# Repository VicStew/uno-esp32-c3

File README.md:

# ESP32-C6 Dev Board
Personal project involving the creation of an ESP32-C6 Dev Board. 

The ESP32-C6 module comes equipped with:
* A 32-bit processor with a clock speed of upto 160 MHz. 
* Supports Wi-Fi 6 and bluetooth 5 (LE) with onboard antenna and thread, zigbee protocols.
* Comes with built in 320KB ROM, 512KB of HP SRAM, 16KB LP SRAM and 4MB Flash memory.
* Adapts multiple IO interfaces and integrates a full-speed USB PHY interface.

The Dev Board includes support for DC input power.

## Getting Started

## Development Environment Setup (Ubuntu)

This project supports firmware development for the **ESP32-C6** using both:

* **C/C++ with ESP-IDF** (official Espressif framework)
* **Rust with esp-rs** (modern, type-safe embedded development)

You can use either workflow independently.

---

## Option A: C/C++ Development (ESP-IDF)

ESP-IDF is Espressif’s official SDK and provides full, first-class support for the ESP32-C6.

### 1. Install System Dependencies

Update your system and install required packages:

```bash
sudo apt update
sudo apt install -y \
  git \
  python3 \
  python3-pip \
  python3-venv \
  cmake \
  ninja-build \
  libusb-1.0-0
```

Verify Python:

```bash
python3 --version
```

---

### 2. Install ESP-IDF

Clone ESP-IDF (recommended stable version):

```bash
git clone -b v5.2 --recursive https://github.com/espressif/esp-idf.git
```

Run the installer:

```bash
cd esp-idf
./install.sh esp32c6
```

Activate the ESP-IDF environment:

```bash
source export.sh
```

To make this persistent, you may add the above line to your `~/.bashrc` or `~/.zshrc`.

Verify installation:

```bash
idf.py --version
```

---

### 3. First Hello World (C/C++)

Create a new project:

```bash
idf.py create-project hello_world
cd hello_world
```

Set the target to ESP32-C6:

```bash
idf.py set-target esp32c6
```

(Optional) Configure the project:

```bash
idf.py menuconfig
```

Important settings:

* Serial port selection
* Flash size (if your PCB differs from defaults)

Build, flash, and monitor:

```bash
idf.py build
idf.py flash monitor
```

Expected serial output:

```
Hello world!
```

Your toolchain is alive and talking.

---

## Option B: Rust Development (esp-rs)

Rust development uses the esp-hal ecosystem and the RISC-V toolchain for ESP32-C6.

---

### 1. Install Rust

Install Rust using `rustup`:

```bash
curl --proto '=https' --tlsv1.2 -sSf https://sh.rustup.rs | sh
```

Reload your shell:

```bash
source ~/.cargo/env
```

Install required components:

```bash
rustup component add rust-src
```

---

### 2. Install ESP Rust Toolchain

Install the ESP toolchain manager:

```bash
cargo install espup
```

Install ESP targets and tools:

```bash
espup install
```

Activate the environment:

```bash
source ~/export-esp.sh
```

Add the ESP32-C6 target:

```bash
rustup target add riscv32imac-unknown-none-elf
```

---

### 3. First Hello World (Rust)

Install the project generator:

```bash
cargo install esp-generate
```

Create a new project:

```bash
cargo generate esp-rs/esp-template
```

During setup:

* Select **esp32c6**
* Choose **no_std**
* Enable **UART logging**

Navigate into the project:

```bash
cd your_project_name
```

Build and flash:

```bash
cargo run
```

Expected output over serial:

```
Hello world from Rust!
```

Rust is officially on the board 🦀.

---

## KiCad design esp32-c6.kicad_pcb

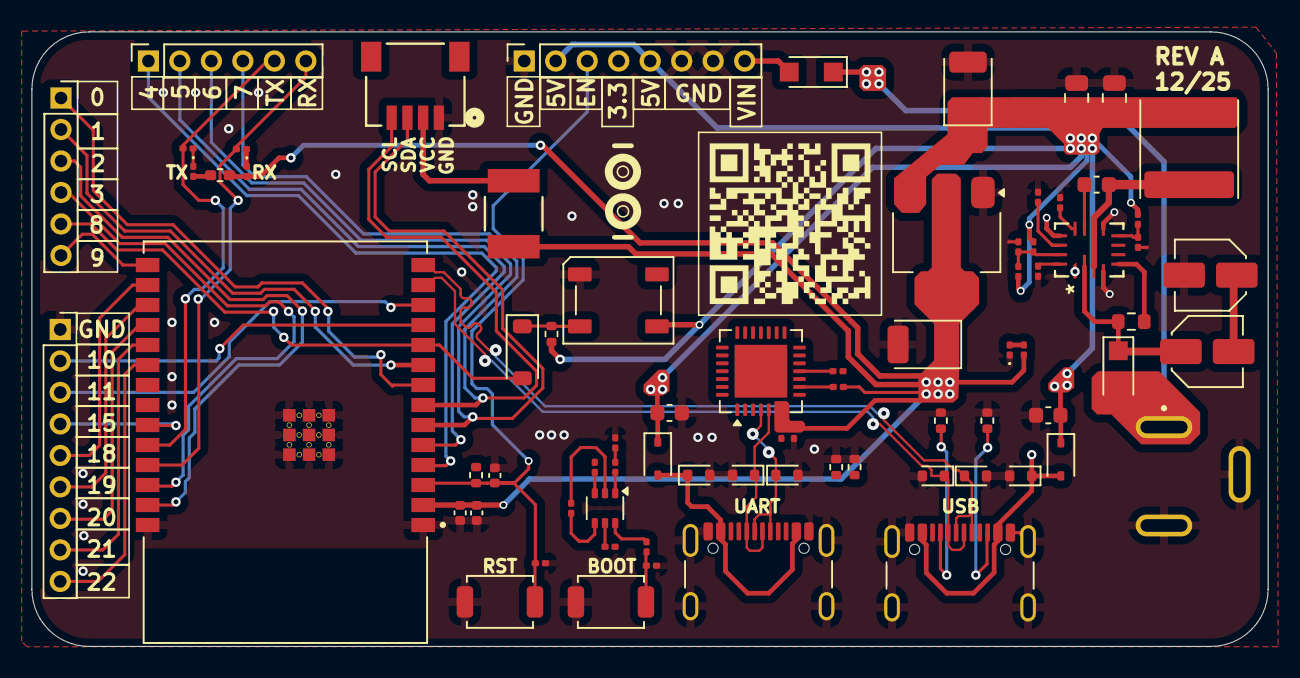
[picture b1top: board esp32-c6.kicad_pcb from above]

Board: 2 copper layers, 78.5 x 39.0 mm, 75 parts (0 on the bottom side), 60 nets.

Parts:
C1, C2: 10u/25V; C_0603_1608Metric
C3: 4.7u; C_0201_0603Metric
C4, C5, C6: 0.1u; C_0201_0603Metric
C7: 1u; C_0402_1005Metric
C8: 0.1u; C_0603_1608Metric
C9, C10: 22u, 25V; C_Elec_4x5.4
C11: 10p; C_0201_0603Metric
C12, C13: 22u; C_0805_2012Metric
C14, C17: 1u; C_0201_0603Metric
C15: 4.7n; C_0201_0603Metric
C16, C18: 10u; CP_EIA-3528-12_Kemet-T
C19: 0.1u; C_0402_1005Metric
C20: 10u; C_0402_1005Metric
D1, D2, D3, D4, D5, D13: ESD5Zxx; D_SOD-523
D6, D14: 1N5819WS; D_SOD-323
D7: 1N4148W; D_SOD-123
D8: WS2812B; LED_WS2812B_PLCC4_5.0x5.0mm_P3.2mm
D9, D10: PMEG6020AELR; Nexperia_CFP3_SOD-123W
D11, D12, D15: LED; LED_0201_0603Metric
F1: Polyfuse; FUSE_F050-2
J1, J2: USB_C_Receptacle_USB2.0_14P; USB_C_Receptacle_GCT_USB4105-xx-A_16P_TopMnt_Horizontal
J3: 54-00166; TENSILITY_54-00166
J4: Conn_01x08_Socket; PinSocket_1x08_P2.00mm_Vertical
J5, J8: Conn_01x06_Socket; PinSocket_1x06_P2.00mm_Vertical
J6: Conn_01x04; CONN_SM04B-SRSS-TB_JST
J9: Conn_01x09_Socket; PinSocket_1x09_P2.00mm_Vertical
L1: 10u; L_Changjiang_FNR6045S
Q1: BC847BDW1; SOT-363_SC-70-6
R1, R2, R3, R4: 5.1k; R_0402_1005Metric
R5, R15: 10k; R_0402_1005Metric
R6: 0; R_0402_1005Metric_Pad0.72x0.64mm_HandSolder
R7: 1k; R_0201_0603Metric
R8, R12, R13: 0; R_0201_0603Metric
R9, R10, R11, R14: 10k; R_0201_0603Metric
R16: 68.1k; R_0201_0603Metric
R17: 13k; R_0201_0603Metric
R18: 100k; R_0603_1608Metric
R19: 169k; R_0201_0603Metric
R20: 10; R_0201_0603Metric
R21, R22: 330; R_0201_0603Metric
R23: 5.1k; R_0201_0603Metric
SW1, SW2: SW_Push; SW_SPST_TS-1088-xR020
U1: CP2102N-Axx-xQFN28; QFN-28-1EP_5x5mm_P0.5mm_EP3.35x3.35mm
U2: MPQ9841GLE-5-AEC1-Z; QFN-16_MPQ9841
U3: NCP1117-3.3_SOT223; SOT-223-3_TabPin2
U4: ESP32-C6-WROOM-1-N8; XCVR_ESP32-C6-WROOM-1-N8

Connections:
+3.3V: C3.1, C4.1, C18.1, C19.1, C20.1, D11.2 (A), D12.2 (A), F1.2, J4.4, R6.1, R6.2, R7.1, R15.1, R23.1, U1.6 (VDD), U1.7 (VREGIN), U3.2 (VO), U4.2 (3V3)
+5V: C1.1, C2.1, C11.1, C12.1, C13.1, C16.1, D6.1 (K), D8.1 (VDD), D14.1 (K), J4.2, J4.5, L1.2, R5.1, R16.1, R20.1, U3.3 (VI)
/Barrel Jack/<NO NET>: C8.2, L1.1, U2.3 (SW), U2.10 (SW)
/Barrel Jack/BIAS: C17.1, R20.2, U2.8 (BIAS)
/Barrel Jack/BST: C8.1, U2.11 (BST)
/Barrel Jack/EN: R18.2, U2.5 (EN)
/Barrel Jack/FREQ: R19.1, U2.16 (FREQ)
/Barrel Jack/VOUT: C11.2, R16.2, R17.1, U2.15 (VOUT)
/DA_N: D5.1 (K), J1.A7 (D-), J1.B7 (D-), U1.5 (D-)
/DA_P: D3.1 (K), J1.A6 (D+), J1.B6 (D+), U1.4 (D+)
/DTR: R9.2, R11.2, U1.28 (~DTR)
/GPIO9: C5.2, R8.1, SW1.2
/RTS: Q1.4 (E2), R10.1, U1.24 (~RTS)
/esp32-c6 Pinout/IO0: J5.1, U4.8 (IO0)
/esp32-c6 Pinout/IO1: J5.2, U4.9 (IO1)
/esp32-c6 Pinout/IO2: J5.3, U4.27 (IO2)
/esp32-c6 Pinout/IO3: J5.4, U4.26 (IO3)
/esp32-c6 Pinout/IO4_TMS: J8.1, U4.4 (IO4)
/esp32-c6 Pinout/IO5_TDI: J8.2, U4.5 (IO5)
/esp32-c6 Pinout/IO6_SDA: J6.3, J8.3, U4.6 (IO6)
/esp32-c6 Pinout/IO7_SCL: J6.4, J8.4, U4.7 (IO7)
/esp32-c6 Pinout/IO9_BOOT: J5.6, U4.15 (IO9)
/esp32-c6 Pinout/IO10: J9.2, U4.11 (IO10)
/esp32-c6 Pinout/IO11: J9.3, U4.12 (IO11)
/esp32-c6 Pinout/IO15: J9.4, U4.23 (IO15)
/esp32-c6 Pinout/IO18: J9.5, U4.16 (IO18)
/esp32-c6 Pinout/IO19: J9.6, U4.17 (IO19)
/esp32-c6 Pinout/IO20: J9.7, U4.18 (IO20)
/esp32-c6 Pinout/IO21: J9.8, U4.19 (IO21)
/esp32-c6 Pinout/IO22: J9.9, U4.20 (IO22)
/esp32-c6 Pinout/UART_RX: J8.6, R22.2, U4.25 (TXD0/GPIO16)
/esp32-c6 Pinout/UART_TX: J8.5, R21.2, U4.24 (RXD0/GPIO17)
DB_N: D4.1 (K), J2.A7 (D-), J2.B7 (D-), U4.13 (IO12)
DB_P: D1.1 (K), J2.A6 (D+), J2.B6 (D+), U4.14 (IO13)
EN: C6.2, C7.1, J4.3, R15.2, SW2.2, U4.3 (EN)
GND: C1.2, C2.2, C3.2, C4.2, C5.1, C6.1, C7.2, C10.2, C12.2, C13.2, C14.2, C15.2, C16.2, C17.2, C18.2, C19.2, C20.2, D1.2 (A), D2.2 (A), D3.2 (A), D4.2 (A), D5.2 (A), D8.3 (VSS), D13.2 (A), D15.1 (K), J1.A1 (GND), J1.A12 (GND), J1.B1 (GND), J1.B12 (GND), J1.S1 (SHIELD), J2.A1 (GND), J2.A12 (GND), J2.B1 (GND), J2.B12 (GND), J2.S1 (SHIELD), J3.B, J3.C, J4.1, J4.6, J4.7, J6.1, J9.1, R1.2, R2.2, R3.2, R4.2, R11.1, R12.2, R14.2, R17.2, R19.2, SW1.1, SW2.1, U1.3 (GND), U1.29 (GND), U2.1 (PHASE), U2.4 (PGND), U2.9 (PGND), U2.13 (AGND), U3.1 (GND), U4.1 (GND), U4.28 (GND), U4.29_1 (GND), U4.29_2 (GND), U4.29_3 (GND), U4.29_4 (GND), U4.29_5 (GND), U4.29_6 (GND), U4.29_7 (GND), U4.29_8 (GND), U4.29_9 (GND)
IO8: D7.1 (K), J5.5, U4.10 (IO8)
unnamed: C9.2, C10.1
unnamed: D7.2 (A), D8.4 (DIN), R5.2
unnamed: D10.2 (A), J4.8
unnamed: D11.1 (K), R21.1
unnamed: D12.1 (K), R22.1
unnamed: D15.2 (A), R23.2
unnamed: J1.A5 (CC1), R3.1
unnamed: J1.B5 (CC2), R1.1
unnamed: J2.A5 (CC1), R4.1
unnamed: J2.B5 (CC2), R2.1
unnamed: F1.1, J6.2
unnamed: Q1.2 (B1), R10.2
unnamed: Q1.6 (C1), R8.2
unnamed: Q1.1 (E1), R9.1
unnamed: Q1.5 (B2), R12.1
unnamed: Q1.3 (C2), R13.2
unnamed: R7.2, U1.9 (~RST)
unnamed: R14.1, U1.11 (~SUSPEND)
unnamed: C15.1, U2.14 (SS)
unnamed: C14.1, U2.12 (VCC)
VBUS_A: D2.1 (K), D6.2 (A), J1.A4 (VBUS), J1.A9 (VBUS), J1.B4 (VBUS), J1.B9 (VBUS), U1.8 (VBUS)
VBUS_B: D13.1 (K), D14.2 (A), J2.A4 (VBUS), J2.A9 (VBUS), J2.B4 (VBUS), J2.B9 (VBUS)
VIN: C9.1, D9.1 (K), D9.2 (A), D10.1 (K), J3.A, R18.1, U2.2 (VIN)

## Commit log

2025-11-15 initial commit: usb to uart
2025-11-20 usb-to-uart bridge change
2025-11-23 wroom change + boot & reset
2025-11-24 barrel jack mpq9841 +
2025-11-25 NCP1117-3.3 change
2025-11-29 header pins + footprint assignment
2025-12-08 pcb component layout
2025-12-12 layout + power pin traces
2025-12-19 final tracing + pcb layers + colors
2025-12-20 minor silkscreen changes + readme file
2025-12-20 MPQ9841GLE-5-AEC1-Z model + image update
2026-01-02 Refinement to pcb and schematic layout
2026-01-02 README image update
